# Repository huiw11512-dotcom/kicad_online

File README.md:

# Linux MiniHost A1

RK3568 ARM64 Linux SBC。目标是树莓派 4B 级别的独立 Linux 单板计算机，优先保证稳定启动、存储、显示、网络和 USB 接口；不宣称与树莓派 4B 的 CPU 性能相同。

## Rev1 首板基线

| 模块 | 首板方案 |
|---|---|
| SoC | Rockchip RK3568，FCBGA636 |
| RAM | 2GB LPDDR4X x32，Micron MT53E512M32D1ZW-046B WT:B，单颗、单 Die、单 Rank |
| 系统存储 | 32GB eMMC 5.1，Samsung KLMBG2JETD-B041 候选 |
| 扩展存储 | MicroSD，SDMMC0 4-bit |
| PMIC | RK809-5 |
| CPU 电源 | TCS4525_WT 独立动态 Buck，待完整时序与负载验证 |
| 输入 | USB-C PD 15V/3A |
| 主电源 | LM76005，15V_IN → 5V_SYS，5A 额定设计目标 |
| 预 PMIC 电源 | TPS62132，5V_SYS → 3.3V |
| PCB | 六层 FR-4；1.6mm 为初始目标，最终叠层与阻抗由板厂确认 |

4GB LPDDR4X 保留为后续容量版本，不混入本次 2GB 首板 BOM。4GB 候选虽也出现在公开 Rockchip DDR AVL v3.01 的 RK3568 T/A 项中，但其 D2/FW 双 Die 组织需要单独确认 rank、模板、BIN 与封装映射。

## 当前工程状态（2026-11-16）

**DESIGN IN PROGRESS — DO NOT FABRICATE**

KiCad 主工程已建立层级原理图：**1 张根页 + 12 张子页**。当前源文件结构如下：

1. 根页：USB-C PD、输入保护、15V→5V Buck
2. RK809-5 PMIC
3. DDR 电源
4. 预 PMIC 3.3V 电源
5. RK3568 SoC（17 个 unit）
6. CPU 动态 Buck
7. 32GB eMMC
8. Boot、时钟、复位、UART2 与 Recovery
9. Micron 2GB LPDDR4X
10. MicroSD
11. USB3 HOST1 与 USB-C OTG0 下载/恢复
12. USB2 HOST2/HOST3 两个独立 Type-A Host
13. 初步 Gigabit Ethernet PHY / MagJack 页面

### 已完成的源文件核对

- RK3568：636 个唯一球位；Pin assignment CSV 为 610 个已分配网络 + 26 个显式 NC。
- SoC 原理图 global labels 与 CSV 做坐标级交叉核对：0 个网络标签错配；26 个 NC 标记与 CSV 一致。
- USB2 HOST2/3：SoC R1/R2 对应 HOST2 D−/D+，T1/T2 对应 HOST3 D−/D+；此前误放在 K17/K18/M12/M17 电源球位上的 USB 标签已纠正。
- Wi-Fi/BT pinmux：由于 GMAC0 RGMII 与 SDMMC1 复用球位冲突，Wi-Fi 临时改分配到 SDMMC2 M0，Bluetooth UART 临时分配 UART8 M0。AP6275S 仍是候选；AMPAK Rev.2.7 与 LCSC C2918717 旧版在 pin33/pin35/pin48 存在差异，模块 padout/RF 端口、内部 Buck 网络和模块页未冻结。
- MicroSD：VCC 由 RK809-5 SWOUT2 控制；R57 0Ω 旁路为 DNP，不得装配。
- Ethernet：RTL8211F-CG + HR911130A 初步页已建立；PHY strap、电源、时钟、RGMII 延时、MagJack 引脚和网表审查仍未关闭。

以上是源文件结构与静态映射检查，不等于 KiCad 原生 ERC、网表、电气规则、PCB DRC 或硬件验证通过。

## 尚未完成

- HDMI 完整电路。
- Wi-Fi/BT 模块电路、AP6275S 50-pad footprint、3.3V VBAT/1.8V VDDIO、37.4MHz 晶体、1.8V/32.768kHz LPO 和唤醒控制。
- Ethernet PHY 逐引脚审查与千兆链路验证。
- 40-pin GPIO 最终 pinmux、电压域和连接器。
- 生产测试点、完整电源预算、热设计和局部去耦审查。
- 整板 PCB 布局尚未开始。

## 打开工程

GitHub 网页预览不会把整个 KiCad 层级工程渲染成一张可编辑原理图。请下载完整的 `hardware/kicad` 目录，保留其中的子原理图、符号库和封装库，再用桌面 KiCad 打开工程文件：

- [KiCad 工程文件 A1.kicad_pro](hardware/kicad/A1.kicad_pro)
- [根原理图 A1.kicad_sch](hardware/kicad/A1.kicad_sch)
- [完整 KiCad 工程目录](hardware/kicad/)
- [KiCad 工程说明](hardware/kicad/README.md)

## 关键设计文件

- [Rev1 主设计基线](docs/A1_MASTER_BASELINE_REV1.md)
- [电气实现决策](docs/A1_ELECTRICAL_DECISIONS_REV1.md)
- [Wi-Fi/BT pinmux 与电气基线](hardware/kicad/docs/A1_WIFI_BT_PINMUX_REV1.md)
- [Ethernet PHY 审查清单](hardware/kicad/docs/A1_ETHERNET_VALIDATION_REV1.md)
- [DDR 选型与兼容性门槛](docs/DDR_COMPATIBILITY_GATE.md)
- [DDR 首轮审计记录](docs/A1_DDR_AUDIT_2026-11-16.md)
- [Rockchip DDR 模板 / BIN 确认请求](docs/RK3568_DDR_FAE_REQUEST.md)

## 投板前硬门槛

1. 取得当前官方 Rockchip DDR AVL、精确模板文件、DDR BIN 和 WDQS 适用说明。
2. 完成 RK809-5 全部电源轨与上电时序逐网核对。
3. 完成 HDMI、Ethernet、Wi-Fi/BT、GPIO 等外围原理图。
4. 用原生 KiCad 执行 ERC、网表导出、封装检查和 PCB DRC。
5. 完成六层叠层、阻抗、DDR 拓扑/长度约束、BGA 扇出和电源完整性审查。
6. 首板完成 DDR Training、eMMC 启动、外设功能和联合压力测试。

在上述门槛关闭前，不发布制造版 Gerber、坐标文件或投板 BOM。

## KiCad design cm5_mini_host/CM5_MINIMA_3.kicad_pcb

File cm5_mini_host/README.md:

# CM5 MiniHost — high-speed carrier development

**Stage:** Rev.A engineering prototype derived from the attributed CM5 MINIMA reference. Native KiCad 10 schematic and PCB have been edited and cloud checked, but the board **has not been fabricated, signal-integrity validated, or released for manufacture**.

## Goal

A genuinely Linux-capable small computer using the **Raspberry Pi Compute Module 5**. Features to retain in our eventual custom revision:

- USB-C external 5 V supply and safe power sequencing
- HDMI display output
- Gigabit Ethernet
- PCIe Gen 2 ×1 to M.2 Key-M NVMe SSD
- USB 2.0 host/user interface (plus Wi-Fi/Bluetooth when the fitted CM5 supports it)
- Boot/service access, status indicators and thermal provisions

Unlike a microcontroller demo, CM5 includes CPU, RAM, and optional eMMC and can run Raspberry Pi OS.

## Origin and licensing

The starting electronic design is **CM5 MINIMA REV3** by Pierluigi Colangeli, source: https://github.com/piecol/CM5_MINIMA_REV3

Source snapshot commit: `6d77314dbbc26c8f5735add30ccb0588816cb71a`.

The original is open hardware under **CERN-OHL-S-2.0**. We retain the upstream license and identify changes in version history. Do not describe the baseline as independently designed or verified in this repository. See `SOURCE_README.md` after import.

## Manufacturing-risk BOM correction

**U602 corrected to Diodes 74LVC1G07SE-7 (JLC/LCSC C67531)** from the physically and logically incorrect SN74LVC1G14DBVR value. The existing schematic describes a non-inverting open-drain 1G07 that sinks the R605/D605 LED branch; original 1G14 was a SOT-23 Schmitt inverter, not pin/function/footprint-equivalent in practice. Both schematic P/N+Value and PCB P/N+Value fields synchronized and validated in KiCad: **ERC 0, hard DRC 2, parity 0, unconnected 0, total DRC 85 unchanged**. [U602 verified fix](U602_BOM_CORRECTION_AUDIT.md) / [root cause and remaining footprint checks](U602_COMPONENT_MISMATCH_REVIEW.md).

**Other footprint findings:** [50 mismatch summary](FOOTPRINT_MISMATCH_PAD_AUDIT.md) and [8 actual pad-by-pad comparison](EIGHT_FOOTPRINT_PAD_DELTA.md). Of the eight flagged devices, U602 had confirmed P/N/logic/package error; U1 LIS3DH and CM5 Module301 have a bottom-side coordinate-mirroring effect that must be normalized before interpreting pad offsets as routing faults; J701 difference involves alternate mounting holes. Do not automatically replace stock footprints to silence warnings.

## Latest verified board status — 2026-11-14

**Latest MiniHost-specific native KiCad 10.0.8 run:** [CI run 43606720543](https://github.com/huiw11512-dotcom/kicad_online/actions/runs/43606720543). Results: **ERC 0 errors / 41 warnings; PCB DRC 0 hard errors / 73 warnings; 0 unconnected pads; 0 schematic-to-PCB footprint parity errors.** The 73 PCB warnings are 49 embedded-vs-library footprint differences, 15 silk-edge, 8 silk-overlap and 1 silk-over-copper. They are still subject to review; no warning classes have been globally disabled.

The two RJ45 shield pad-to-edge hard errors have now been resolved by a controlled +0.030 mm notch/fillet adjustment and a manufacturer/fabricator-specific 0.20 mm J1 edge-clearance allowance, while retaining the enhanced 0.372 mm target elsewhere. U602 has also been corrected to Diodes 74LVC1G07SE-7 with its vendor SOT-353 land pattern. **The board is still not fabrication released**: ERC warnings, PCB warnings, stackup-controlled SI/PI, thermal/power and enclosure fit remain.

[Latest detailed verification and release gates](REV_A_LATEST_VERIFICATION.md) · [Latest warning-by-warning triage](DRC_WARNING_TRIAGE.md) · [Power and USB review](POWER_AND_USB_REVIEW.md).

## Rev.A completed and verified (2026-11-14)

- Reproduced actual six-layer CM5 Linux carrier in the native KiCad and web viewer.
- Repaired USB-C root bus naming and verified **4/4 D+/D− schematic-net-to-PCB-pad networks match**.
- Routed one tested USB701 A7 N backside branch from 6.4241 to 4.2503 mm copper centerline; before/after **4 → 4 hard DRC** and **0 → 0 unconnected**. This is not SI signoff.
- Recovered **8 custom PCB-embedded footprint types** into locally registered EasyEDA, Samacsys and _pico libraries, passing KiCad export/reimport pad checks.
- Reconciled the M.2 socket schematic's four nonexistent alternative mechanical pins M1..M4 against the installed 2230/2242 connector footprint.
- Adjusted **R701 15k→39k and R702/R703 22k→56k** in the native schematic and PCB for 500mA default-current USB2 host, with no DRC regression.
- Replaced the oversize rectangular RJ45 F.CrtYd with a **closed pad-aware 12-edge courtyard** in both board and project library: hard errors **4→2** and courtyard overlaps **2→0**, no electrical geometry changes.
- Reconciled conflicting duplicate CM5 NPTH drills: Module301 had **2.7 mm** holes, Module302 had **3.0 mm** holes in the very same locations. Preserved 2.7 mm M2.5 mounting holes and removed duplicate 3.0 mm holes, syncing the HSS project footprint. Native cloud report: **holes_co_located 2→0**, and **ERC/hard DRC/parity/unconnected stayed 0/2/0/0**.
- Initialized official KiCad 10 standard global footprint and symbol tables in CI to remove 65 false missing-library warnings; classified remaining DRC warnings without disabling them.
- Removed duplicate large CM5 outline from Module302/HSS only, leaving GPIO body outline and HSS connector marks: **230→198 DRC entries**.
- Properly hid 27 near-zero KiBuzzard autogenerated reference fields (without removing any visible polygon labels): **198→140 DRC entries**.
- Replaced J701 M.2's per-pad mask expansion 0.102→0.020 mm for its 69 SMT pads; copper/pitch untouched and 0.16 mm nominal mask web for a proposed 1oz green LDI process: **140→86**.
- Removed one redundant USB-C D+ via linking two same-layer F.Cu trace endpoints; net parity and DRC remained safe: **86→85**. Two other flagged vias require stub-level inspection and were retained.
- Removed one pad-free PCB-only demonstration logo footprint REF** (upstream license and attribution preserved).
- Latest *verified* electrical/DFM check after these changes: **ERC 0 errors, PCB schematic/footprint parity 0 issues, PCB unconnected 0**, with **2 remaining hard DRC errors** at the Kycon RJ45 shield solder pads and adjacent board-edge opening. Warnings still exist and require review.

## Current blockers / engineering documents

- [Verified RJ45 pad-aware courtyard audit](RJ45_COURTYARD_RESHAPE_AUDIT.md)
- [500mA USB host change audit](USB_POWER_500MA_AUDIT.md)
- [RJ45 physical conflict map](RJ45_MECHANICAL_CONFLICT_MAP.svg) and [manufacturer-grounded mechanical review](RJ45_MECHANICAL_REVIEW.md): J1 pads 15/16 board-edge hard errors resolved; physical connector/enclosure overhang still requires validation; the previous J1/J601 and J1/H102 courtyard overlaps were removed via geometry verified by KiCad
- [M.2 symbol/footprint verification](M2_SYMBOL_VARIANT_AUDIT.md) and [decorative logo cleanup verification](LOGO_CLEANUP_AUDIT.md)
- [Power, USB, CM5 5V/5A budget and startup review](POWER_AND_USB_REVIEW.md)
- [Controlled USB701 reroute and DRC no-regression](USB_REROUTE_AUDIT.md)
- [Actual KiCad 10 DRC warning triage](DRC_WARNING_TRIAGE.md) and [CM5 duplicate NPTH hole repair](CM5_ALIGNMENT_HOLE_AUDIT.md)
- [Original baseline audit — historical, before Rev.A corrections](AUDIT_2026-11-14.md)

**Next implementation gate:** resolve the two RJ45 shield solder land copper-to-edge gap violations based on Kycon's required PCB opening and full enclosure clearance; updated pad-aware courtyard eliminated two false overlaps and was verified with KiCad. Follow with exact factory stackup-controlled differential impedance, component datasheet verification, full PI/thermal checks, and a prototype bring-up plan. No release Gerbers have been approved.

## Open in ZiroEDA

https://designer.ziroeda.com/gh/huiw11512-dotcom/kicad_online/tree/minihost-revA/cm5_mini_host

If the deep link fails, use ZiroEDA → File → Open from GitHub, select `huiw11512-dotcom/kicad_online` → `cm5_mini_host` → `CM5_MINIMA_3.kicad_pro`.

This baseline includes complete routed source files; 3D manufacturer models may be omitted where large. Missing external 3D models do not affect native copper geometry.

## Important

Do **not** order boards based solely on a successful web import. Proper fabrication release requires electrical design review, pin-map and component-footprint verification, stackup and impedance calculation from the board fabricator, complete DRC/ERC closure, Gerber/NC drill and stencil review, and bench bring-up.

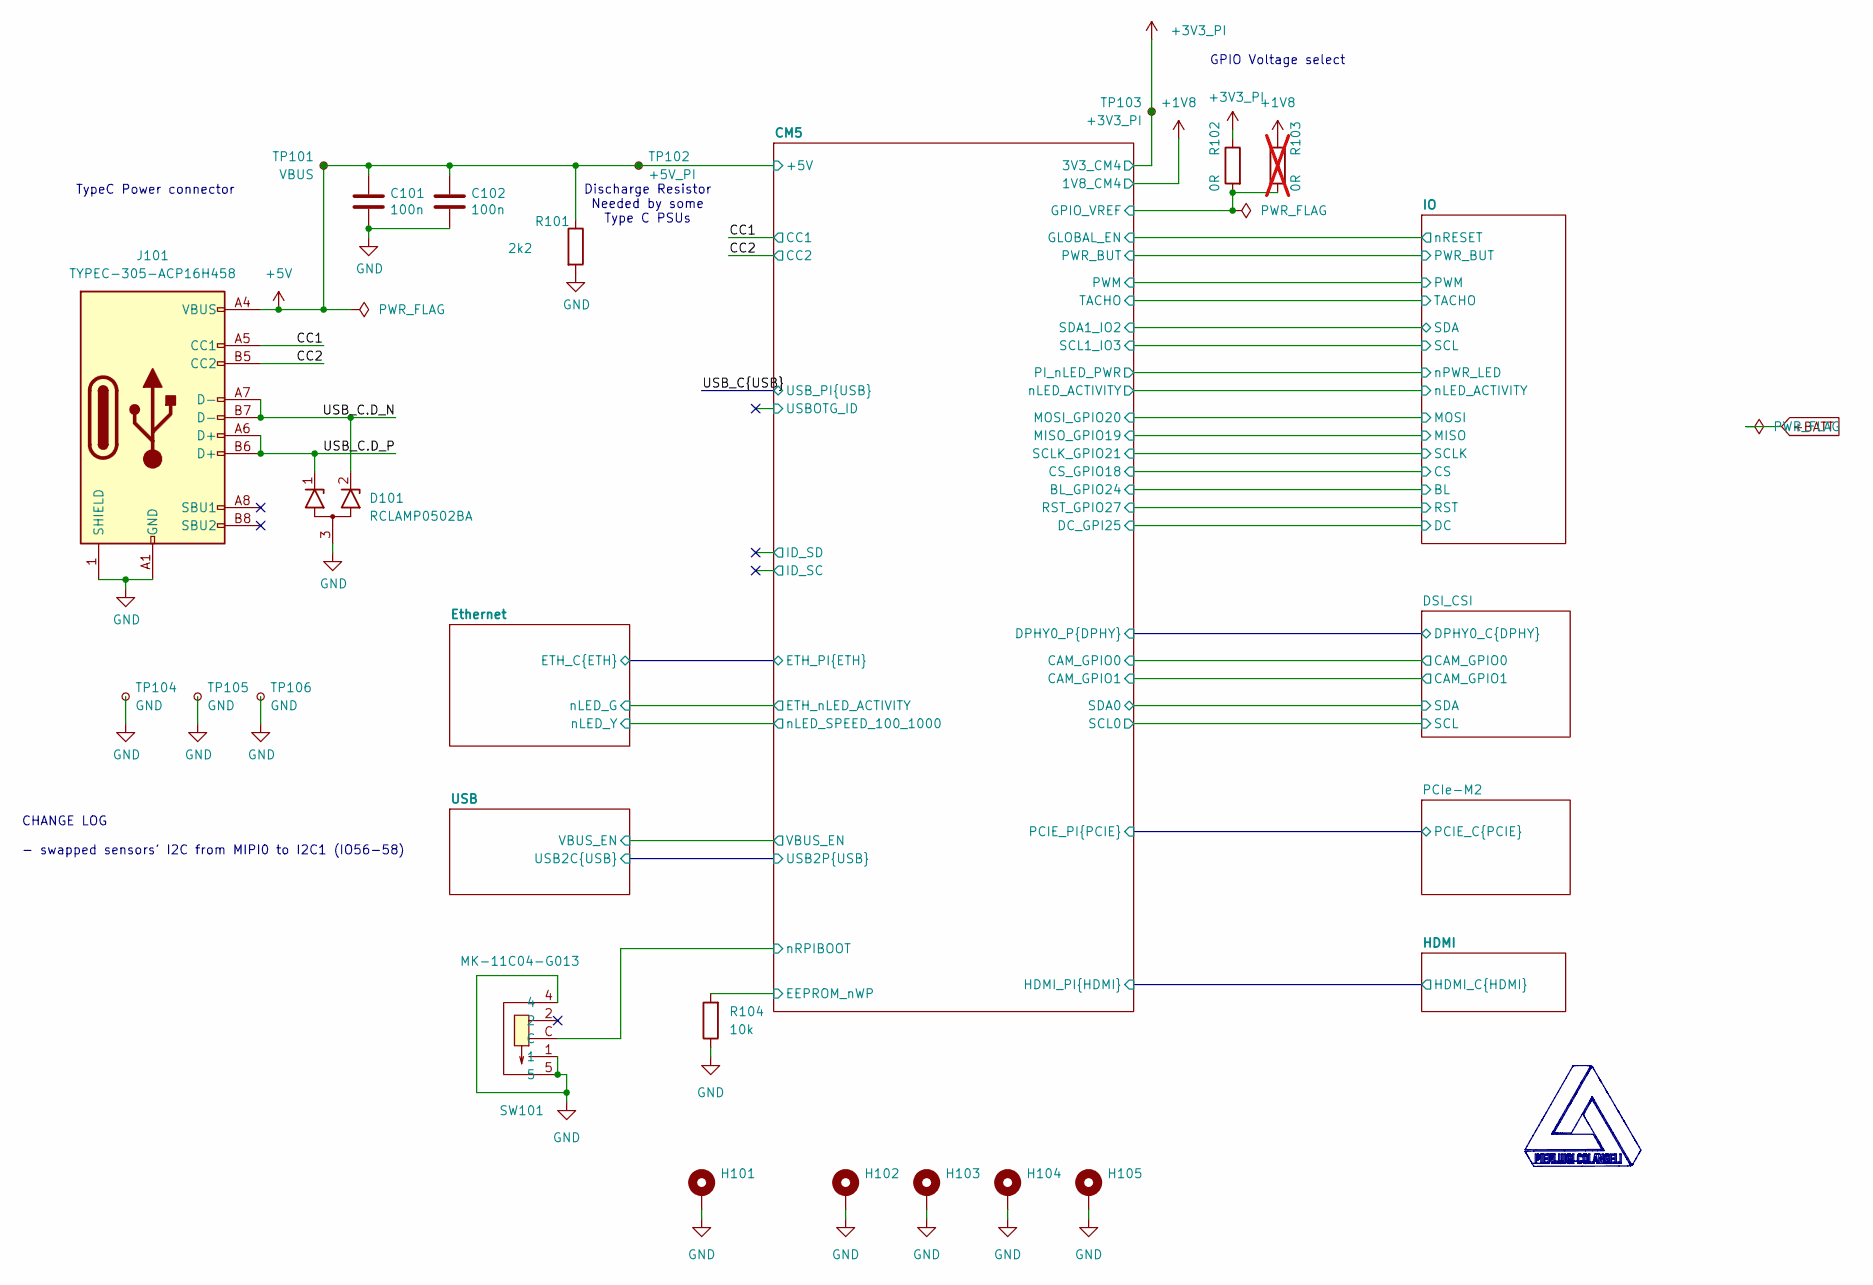
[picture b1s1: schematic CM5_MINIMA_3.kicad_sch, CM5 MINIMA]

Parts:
C101, C102: 100n; C_0402_1005Metric; Part Description 0.1uF 10% 16V Ceramic Capacitor X7R 040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
D101: RCLAMP0502BA; SOT-416
H101: MountingHole_Pad; MountingHole_2.2mm_M2_DIN965_Pad_TopBottom
H102, H103, H104, H105: MountingHole_Pad; MountingHole_2.7mm_Pad
J101: TYPEC-305-ACP16H458; USB-C-SMD_TYPEC-305-ACP16H458; Part Description USBC USB2 data and power connector
R101: 2k2; R_0402_1005Metric
R102: 0R; R_0402_1005Metric; Part Description Resistor 0R M2012 5%
R103: 0R; R_0402_1005Metric; not fitted
R104: 10k; R_0402_1005Metric
SW101: MK-11C04-G013; SW-SMD_MK-11C04-G013; LCSC Part C778185
TP101: VBUS; TestPoint_Pad_D1.0mm__TP101
TP102: +5V_PI; TestPoint_Pad_D1.0mm
TP103: +3V3_PI; TestPoint_Pad_D1.0mm
TP104, TP105, TP106: GND; TestPoint_THTPad_D1.0mm_Drill0.5mm

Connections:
+1V8: R103.1; also elsewhere on the board
+3V3_PI: R102.1, TP103.1; also elsewhere on the board
+5V: C101.1, C102.1, J101.A4 (VBUS), J101.A9 (VBUS), J101.B4 (VBUS), J101.B9 (VBUS), R101.1, TP101.1, TP102.1; also elsewhere on the board
/CC1: J101.A5 (CC1); also elsewhere on the board
/CC2: J101.B5 (CC2); also elsewhere on the board
/CM5/EEPROM_nWP: R104.2; also elsewhere on the board
/CM5/GPIO_VREF: R102.2, R103.2; also elsewhere on the board
/CM5/nRPIBOOT: SW101.C; also elsewhere on the board
/USB_C.D_N: D101.2 (K2), J101.A7 (D-), J101.B7 (D-); also elsewhere on the board
/USB_C.D_P: D101.1 (K1), J101.A6 (D+), J101.B6 (D+); also elsewhere on the board
GND: C101.2, C102.2, D101.3 (A), H101.1, H102.1, H103.1, H104.1, H105.1, J101.1 (SHIELD), J101.A1 (GND), J101.A12 (GND), J101.B1 (GND), J101.B12 (GND), R101.2, R104.1, SW101.1, SW101.4, SW101.5, TP104.1, TP105.1, TP106.1; also elsewhere on the board

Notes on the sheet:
CHANGE LOG - swapped sensors' I2C from MIPI0 to I2C1 (IO56-58)
GPIO Voltage select
TypeC Power connector
Discharge Resistor Needed by some Type C PSUs

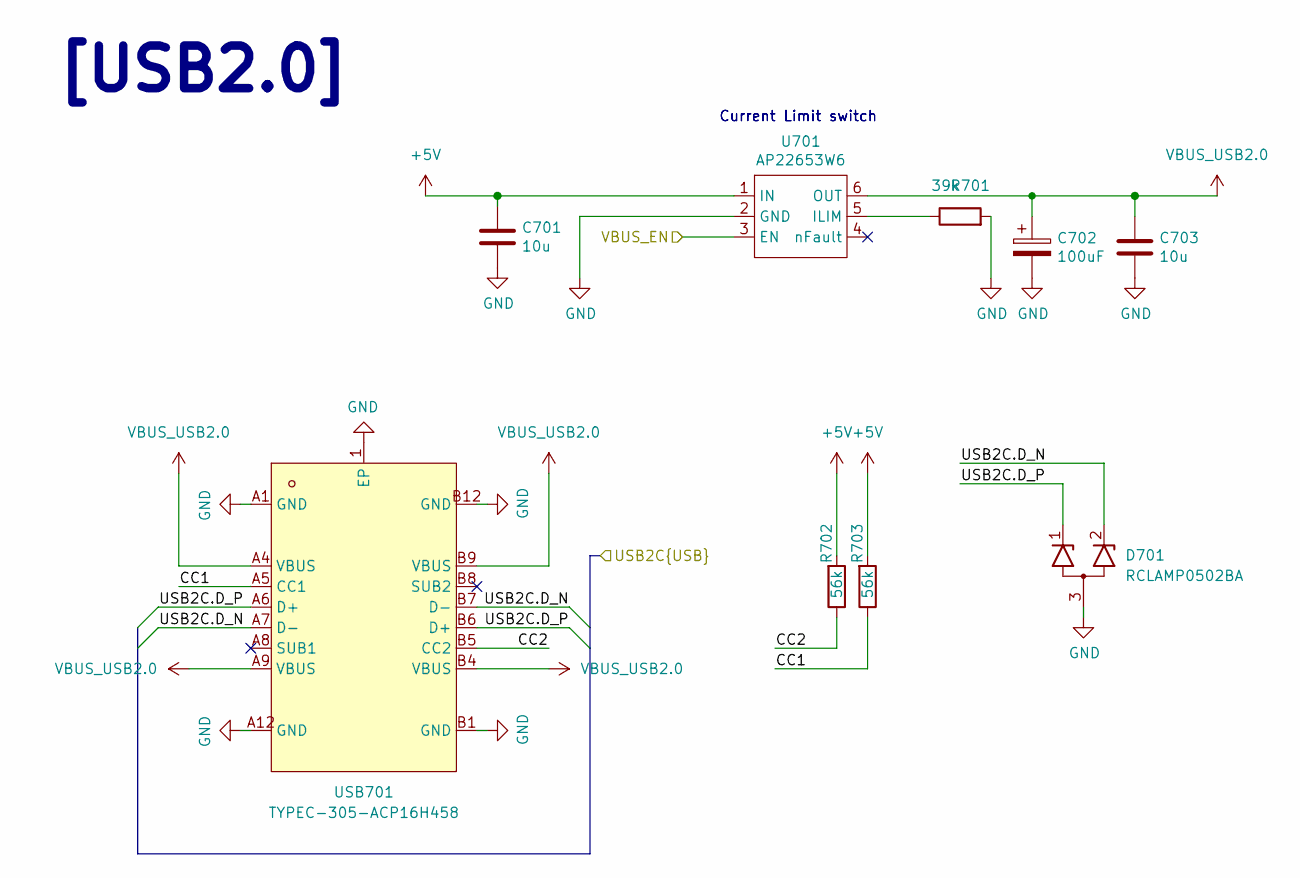
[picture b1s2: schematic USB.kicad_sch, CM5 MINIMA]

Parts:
C701, C703: 10u; C_0805_2012Metric; Part Description 10uF 10% 10V Ceramic Capacitor X7R 0805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
C702: 100uF; CP_EIA-3528-21_Kemet-B; Part Description 100uF 6.3V 1.7Ω@100kHz ±10% CASE-B-3528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
D701: RCLAMP0502BA; SOT-416__D701
R701: 39k; R_0402_1005Metric; Part Description Resistor 15K M1005 1% 63mW
R702, R703: 56k; R_0402_1005Metric__R702__R703
U701: AP22653W6; SOT-23-6; Part Description Power Switch/Driver 1:1 P-Channel 2.1A 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
USB701: TYPEC-305-ACP16H458; USB-C-SMD_TYPEC-305-ACP16H458; LCSC Part C5454943

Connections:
+5V: C701.1, R702.2, R703.2, U701.1 (IN); also elsewhere on the board
/CM5/USB2P.D_N: D701.2 (K2), USB701.A7 (D-), USB701.B7 (D-); also elsewhere on the board
/CM5/USB2P.D_P: D701.1 (K1), USB701.A6 (D+), USB701.B6 (D+); also elsewhere on the board
/CM5/VBUS_EN: U701.3 (EN); also elsewhere on the board
/USB/CC1: R703.1, USB701.A5 (CC1)
/USB/CC2: R702.1, USB701.B5 (CC2)
GND: C701.2, C702.2, C703.2, D701.3 (A), R701.2, U701.2 (GND), USB701.1 (EP), USB701.A1 (GND), USB701.A12 (GND), USB701.B1 (GND), USB701.B12 (GND); also elsewhere on the board
unnamed: R701.1, U701.5 (ILIM)
VBUS_USB2.0: C702.1, C703.1, U701.6 (OUT), USB701.A4 (VBUS), USB701.A9 (VBUS), USB701.B4 (VBUS), USB701.B9 (VBUS)

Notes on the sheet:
[USB2.0]
Current Limit switch

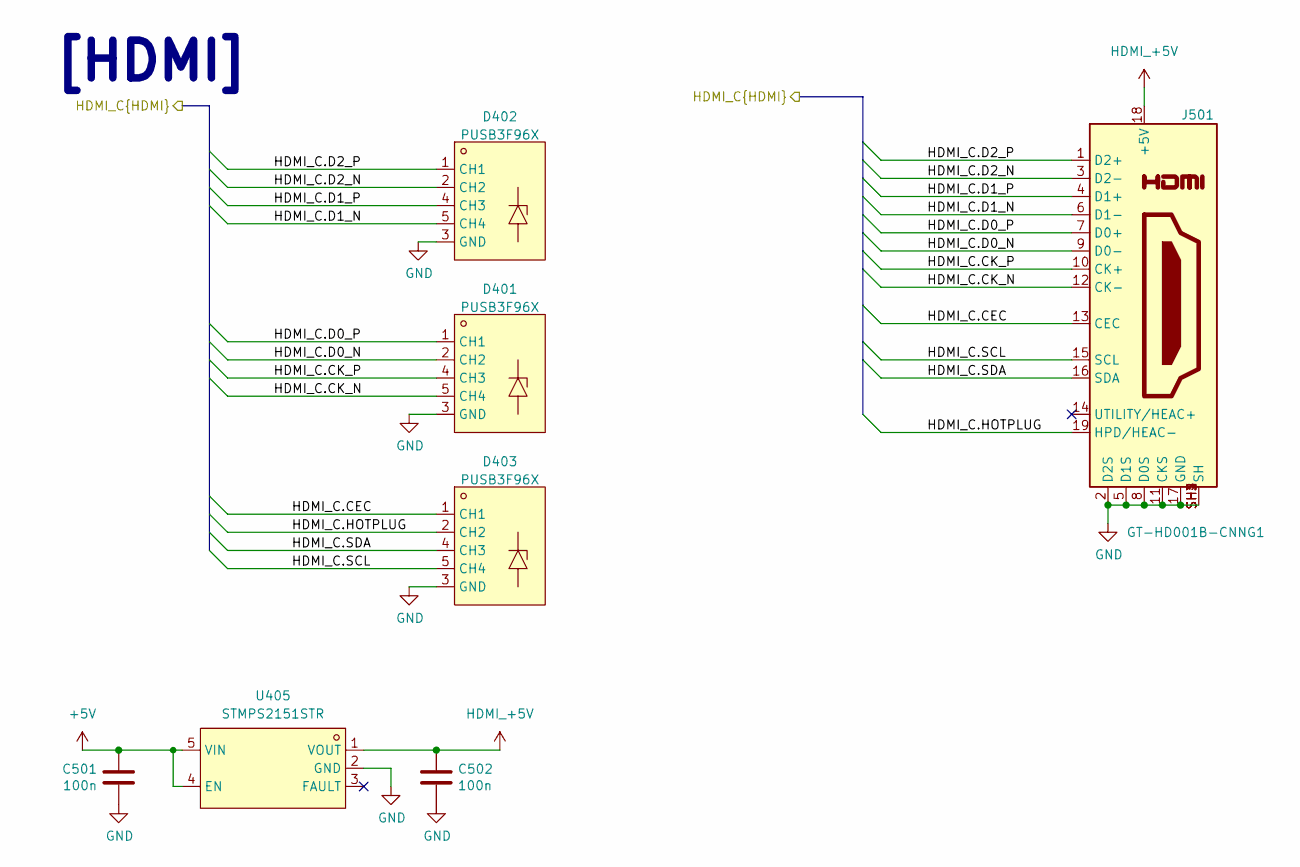
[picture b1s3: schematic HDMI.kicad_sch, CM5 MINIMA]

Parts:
C501, C502: 100n; C_0402_1005Metric; Part Description 0.1uF 10% 16V Ceramic Capacitor X7R 040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
D401, D402, D403: PUSB3F96X; DFN2510A-10_L2.5-W1.0-P0.50-BL; LCSC Part C478121
J501: GT-HD001B-CNNG1; EDAC 690-019-298-412; Part Description HDMI Connector, Right Angle, 19 Contact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
U405: STMPS2151STR; SOT-23-5; LCSC Part C135998

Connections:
+5V: C501.1, U405.4 (EN), U405.5 (VIN); also elsewhere on the board
/CM5/HDMI_PI.CEC: D403.1 (CH1), D403.10 (NC), J501.13 (CEC); also elsewhere on the board
/CM5/HDMI_PI.CK_N: D401.5 (CH4), D401.6 (NC), J501.12 (CK-); also elsewhere on the board
/CM5/HDMI_PI.CK_P: D401.4 (CH3), D401.7 (NC), J501.10 (CK+); also elsewhere on the board
/CM5/HDMI_PI.D0_N: D401.2 (CH2), D401.9 (NC), J501.9 (D0-); also elsewhere on the board
/CM5/HDMI_PI.D0_P: D401.1 (CH1), D401.10 (NC), J501.7 (D0+); also elsewhere on the board
/CM5/HDMI_PI.D1_N: D402.5 (CH4), D402.6 (NC), J501.6 (D1-); also elsewhere on the board
/CM5/HDMI_PI.D1_P: D402.4 (CH3), D402.7 (NC), J501.4 (D1+); also elsewhere on the board
/CM5/HDMI_PI.D2_N: D402.2 (CH2), D402.9 (NC), J501.3 (D2-); also elsewhere on the board
/CM5/HDMI_PI.D2_P: D402.1 (CH1), D402.10 (NC), J501.1 (D2+); also elsewhere on the board
/CM5/HDMI_PI.HOTPLUG: D403.2 (CH2), D403.9 (NC), J501.19 (HPD/HEAC-); also elsewhere on the board
/CM5/HDMI_PI.SCL: D403.5 (CH4), D403.6 (NC), J501.15 (SCL); also elsewhere on the board
/CM5/HDMI_PI.SDA: D403.4 (CH3), D403.7 (NC), J501.16 (SDA); also elsewhere on the board
GND: C501.2, C502.2, D401.3 (GND), D401.8 (GND), D402.3 (GND), D402.8 (GND), D403.3 (GND), D403.8 (GND), J501.2 (D2S), J501.5 (D1S), J501.8 (D0S), J501.11 (CKS), J501.17 (GND), J501.SH1 (SH), J501.SH2 (SH), J501.SH3 (SH), J501.SH4 (SH), U405.2 (GND); also elsewhere on the board
HDMI_+5V: C502.1, J501.18 (+5V), U405.1 (VOUT)

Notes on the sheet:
[HDMI]

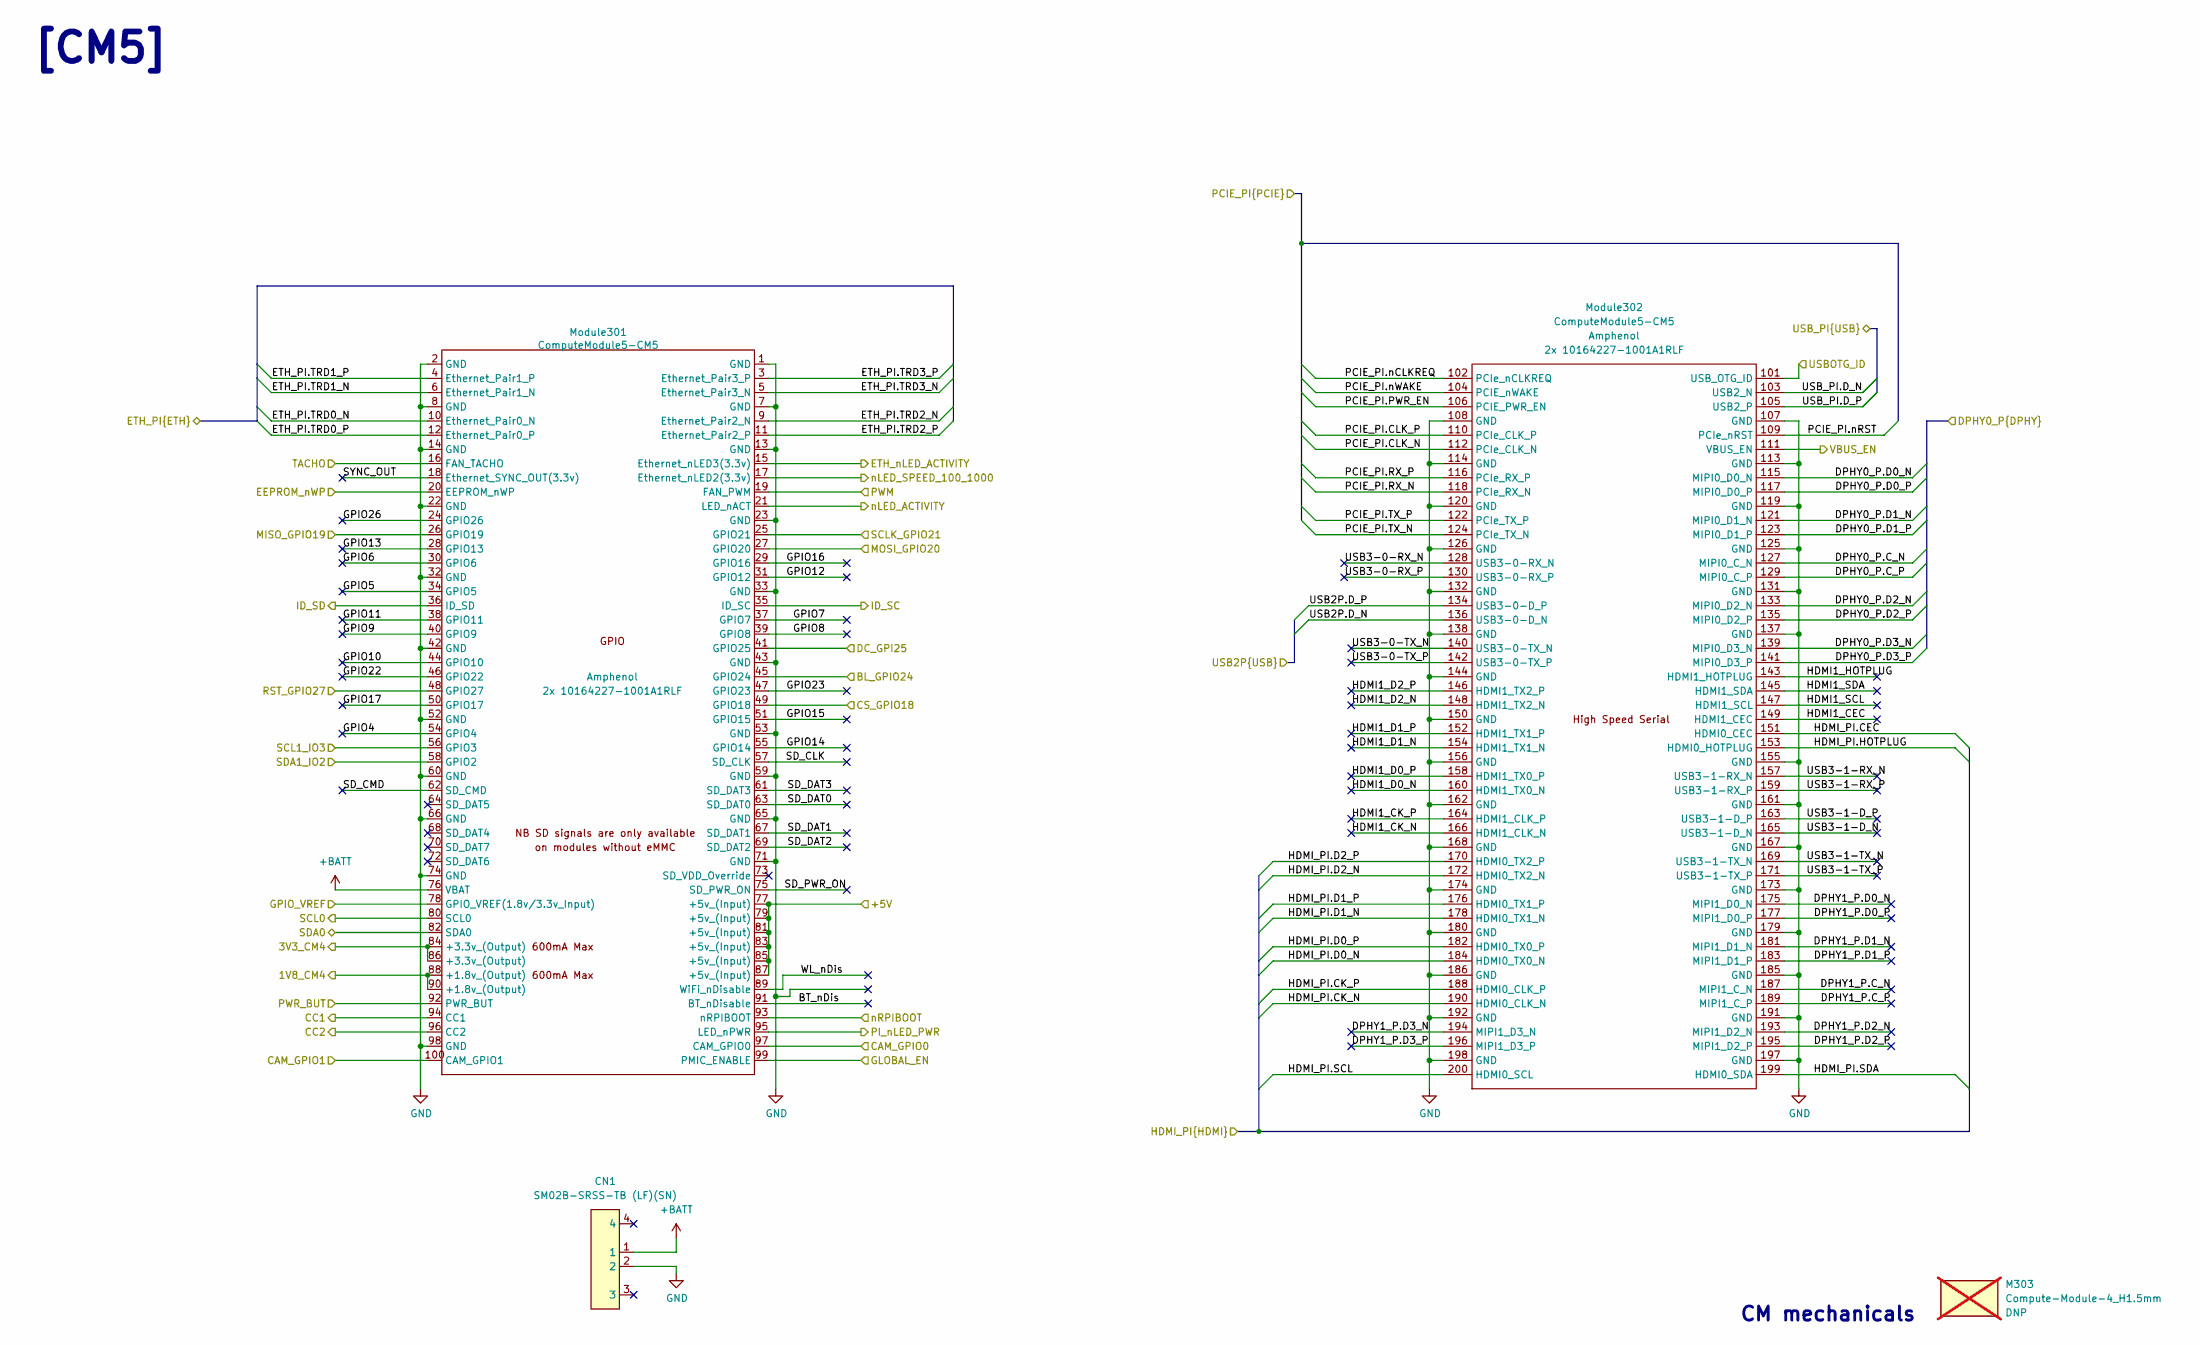
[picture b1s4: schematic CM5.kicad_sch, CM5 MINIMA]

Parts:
CN1: SM02B-SRSS-TB (LF)(SN); CONN-SMD_2P-P1.00_SM02B-SRSS-TB-LF-SN; LCSC Part C160402
M303: Compute-Module-4_H1.5mm; MPN SC0294; not fitted
Module301: ComputeModule5-CM5; Raspberry-Pi-5-Compute-Module_GPIO; Part Description 100 Position Connector Receptacle, Cent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
Module302: ComputeModule5-CM5; Raspberry-Pi-5-Compute-Module_HSS; Part Description 100 Position Connector Receptacle, Cent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

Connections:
+1V8: Module301.88 (+1.8v_(Output)), Module301.90 (+1.8v_(Output)); also elsewhere on the board
+3V3_PI: Module301.84 (+3.3v_(Output)), Module301.86 (+3.3v_(Output)); also elsewhere on the board
+5V: Module301.77 (+5v_(Input)), Module301.79 (+5v_(Input)), Module301.81 (+5v_(Input)), Module301.83 (+5v_(Input)), Module301.85 (+5v_(Input)), Module301.87 (+5v_(Input)); also elsewhere on the board
+BATT: CN1.1, Module301.76 (VBAT)
/CC1: Module301.94 (CC1); also elsewhere on the board
/CC2: Module301.96 (CC2); also elsewhere on the board
/CM5/BL_GPIO24: Module301.45 (GPIO24); also elsewhere on the board
/CM5/BT_nDis: Module301.91 (BT_nDisable)
/CM5/CAM_GPIO0: Module301.97 (CAM_GPIO0); also elsewhere on the board
/CM5/CAM_GPIO1: Module301.100 (CAM_GPIO1); also elsewhere on the board
/CM5/CS_GPIO18: Module301.49 (GPIO18); also elsewhere on the board
/CM5/DC_GPI25: Module301.41 (GPIO25); also elsewhere on the board
/CM5/DPHY0_P.C_N: Module302.127 (MIPI0_C_N); also elsewhere on the board
/CM5/DPHY0_P.C_P: Module302.129 (MIPI0_C_P); also elsewhere on the board
/CM5/DPHY0_P.D0_N: Module302.115 (MIPI0_D0_N); also elsewhere on the board
/CM5/DPHY0_P.D0_P: Module302.117 (MIPI0_D0_P); also elsewhere on the board
/CM5/DPHY0_P.D1_N: Module302.121 (MIPI0_D1_N); also elsewhere on the board
/CM5/DPHY0_P.D1_P: Module302.123 (MIPI0_D1_P); also elsewhere on the board
/CM5/DPHY0_P.D2_N: Module302.133 (MIPI0_D2_N); also elsewhere on the board
/CM5/DPHY0_P.D2_P: Module302.135 (MIPI0_D2_P); also elsewhere on the board
/CM5/DPHY0_P.D3_N: Module302.139 (MIPI0_D3_N); also elsewhere on the board
/CM5/DPHY0_P.D3_P: Module302.141 (MIPI0_D3_P); also elsewhere on the board
/CM5/DPHY1_P.C_N: Module302.187 (MIPI1_C_N)
/CM5/DPHY1_P.C_P: Module302.189 (MIPI1_C_P)
/CM5/DPHY1_P.D0_N: Module302.175 (MIPI1_D0_N)
/CM5/DPHY1_P.D0_P: Module302.177 (MIPI1_D0_P)
/CM5/DPHY1_P.D1_N: Module302.181 (MIPI1_D1_N)
/CM5/DPHY1_P.D1_P: Module302.183 (MIPI1_D1_P)
/CM5/DPHY1_P.D2_N: Module302.193 (MIPI1_D2_N)
/CM5/DPHY1_P.D2_P: Module302.195 (MIPI1_D2_P)
/CM5/DPHY1_P.D3_N: Module302.194 (MIPI1_D3_N)
/CM5/DPHY1_P.D3_P: Module302.196 (MIPI1_D3_P)
/CM5/EEPROM_nWP: Module301.20 (EEPROM_nWP); also elsewhere on the board
/CM5/ETH_PI.TRD0_N: Module301.10 (Ethernet_Pair0_N); also elsewhere on the board
/CM5/ETH_PI.TRD0_P: Module301.12 (Ethernet_Pair0_P); also elsewhere on the board
/CM5/ETH_PI.TRD1_N: Module301.6 (Ethernet_Pair1_N); also elsewhere on the board
/CM5/ETH_PI.TRD1_P: Module301.4 (Ethernet_Pair1_P); also elsewhere on the board
/CM5/ETH_PI.TRD2_N: Module301.9 (Ethernet_Pair2_N); also elsewhere on the board
/CM5/ETH_PI.TRD2_P: Module301.11 (Ethernet_Pair2_P); also elsewhere on the board
/CM5/ETH_PI.TRD3_N: Module301.5 (Ethernet_Pair3_N); also elsewhere on the board
/CM5/ETH_PI.TRD3_P: Module301.3 (Ethernet_Pair3_P); also elsewhere on the board
/CM5/ETH_nLED_ACTIVITY: Module301.15 (Ethernet_nLED3(3.3v)); also elsewhere on the board
/CM5/GLOBAL_EN: Module301.99 (PMIC_ENABLE)
/CM5/GPIO4: Module301.54 (GPIO4)
/CM5/GPIO5: Module301.34 (GPIO5)
/CM5/GPIO6: Module301.30 (GPIO6)
/CM5/GPIO7: Module301.37 (GPIO7)
/CM5/GPIO8: Module301.39 (GPIO8)
/CM5/GPIO9: Module301.40 (GPIO9)
/CM5/GPIO10: Module301.44 (GPIO10)
/CM5/GPIO11: Module301.38 (GPIO11)
/CM5/GPIO12: Module301.31 (GPIO12)
/CM5/GPIO13: Module301.28 (GPIO13)
/CM5/GPIO14: Module301.55 (GPIO14)
/CM5/GPIO15: Module301.51 (GPIO15)
/CM5/GPIO16: Module301.29 (GPIO16)
/CM5/GPIO17: Module301.50 (GPIO17)
/CM5/GPIO22: Module301.46 (GPIO22)
/CM5/GPIO23: Module301.47 (GPIO23)
/CM5/GPIO26: Module301.24 (GPIO26)
/CM5/GPIO_VREF: Module301.78 (GPIO_VREF(1.8v/3.3v_Input)); also elsewhere on the board
/CM5/HDMI1_CEC: Module302.149 (HDMI1_CEC)
/CM5/HDMI1_CK_N: Module302.166 (HDMI1_CLK_N)
/CM5/HDMI1_CK_P: Module302.164 (HDMI1_CLK_P)
/CM5/HDMI1_D0_N: Module302.160 (HDMI1_TX0_N)
/CM5/HDMI1_D0_P: Module302.158 (HDMI1_TX0_P)
/CM5/HDMI1_D1_N: Module302.154 (HDMI1_TX1_N)
/CM5/HDMI1_D1_P: Module302.152 (HDMI1_TX1_P)
/CM5/HDMI1_D2_N: Module302.148 (HDMI1_TX2_N)
/CM5/HDMI1_D2_P: Module302.146 (HDMI1_TX2_P)
/CM5/HDMI1_HOTPLUG: Module302.143 (HDMI1_HOTPLUG)
/CM5/HDMI1_SCL: Module302.147 (HDMI1_SCL)
/CM5/HDMI1_SDA: Module302.145 (HDMI1_SDA)
/CM5/HDMI_PI.CEC: Module302.151 (HDMI0_CEC); also elsewhere on the board
/CM5/HDMI_PI.CK_N: Module302.190 (HDMI0_CLK_N); also elsewhere on the board
/CM5/HDMI_PI.CK_P: Module302.188 (HDMI0_CLK_P); also elsewhere on the board
/CM5/HDMI_PI.D0_N: Module302.184 (HDMI0_TX0_N); also elsewhere on the board
/CM5/HDMI_PI.D0_P: Module302.182 (HDMI0_TX0_P); also elsewhere on the board
/CM5/HDMI_PI.D1_N: Module302.178 (HDMI0_TX1_N); also elsewhere on the board
/CM5/HDMI_PI.D1_P: Module302.176 (HDMI0_TX1_P); also elsewhere on the board
/CM5/HDMI_PI.D2_N: Module302.172 (HDMI0_TX2_N); also elsewhere on the board
/CM5/HDMI_PI.D2_P: Module302.170 (HDMI0_TX2_P); also elsewhere on the board
/CM5/HDMI_PI.HOTPLUG: Module302.153 (HDMI0_HOTPLUG); also elsewhere on the board
/CM5/HDMI_PI.SCL: Module302.200 (HDMI0_SCL); also elsewhere on the board
/CM5/HDMI_PI.SDA: Module302.199 (HDMI0_SDA); also elsewhere on the board
/CM5/ID_SC: Module301.35 (ID_SC)
/CM5/ID_SD: Module301.36 (ID_SD)
/CM5/MISO_GPIO19: Module301.26 (GPIO19); also elsewhere on the board
/CM5/MOSI_GPIO20: Module301.27 (GPIO20); also elsewhere on the board
/CM5/PCIE_PI.CLK_N: Module302.112 (PCIe_CLK_N); also elsewhere on the board
/CM5/PCIE_PI.CLK_P: Module302.110 (PCIe_CLK_P); also elsewhere on the board
/CM5/PCIE_PI.PWR_EN: Module302.106 (PCIE_PWR_EN); also elsewhere on the board
/CM5/PCIE_PI.RX_N: Module302.118 (PCIe_RX_N); also elsewhere on the board
/CM5/PCIE_PI.RX_P: Module302.116 (PCIe_RX_P); also elsewhere on the board
/CM5/PCIE_PI.TX_N: Module302.124 (PCIe_TX_N); also elsewhere on the board
/CM5/PCIE_PI.TX_P: Module302.122 (PCIe_TX_P); also elsewhere on the board
/CM5/PCIE_PI.nCLKREQ: Module302.102 (PCIe_nCLKREQ); also elsewhere on the board
/CM5/PCIE_PI.nRST: Module302.109 (PCIe_nRST); also elsewhere on the board
/CM5/PCIE_PI.nWAKE: Module302.104 (PCIE_nWAKE); also elsewhere on the board
/CM5/PI_nLED_PWR: Module301.95 (LED_nPWR); also elsewhere on the board
/CM5/PWM: Module301.19 (FAN_PWM); also elsewhere on the board
/CM5/PWR_BUT: Module301.92 (PWR_BUT); also elsewhere on the board
/CM5/RST_GPIO27: Module301.48 (GPIO27); also elsewhere on the board
/CM5/SCL0: Module301.80 (SCL0); also elsewhere on the board
/CM5/SCLK_GPIO21: Module301.25 (GPIO21); also elsewhere on the board
/CM5/SDA0: Module301.82 (SDA0); also elsewhere on the board
/CM5/SD_CLK: Module301.57 (SD_CLK)
/CM5/SD_CMD: Module301.62 (SD_CMD)
/CM5/SD_DAT0: Module301.63 (SD_DAT0)
/CM5/SD_DAT1: Module301.67 (SD_DAT1)
/CM5/SD_DAT2: Module301.69 (SD_DAT2)
/CM5/SD_DAT3: Module301.61 (SD_DAT3)
/CM5/SD_PWR_ON: Module301.75 (SD_PWR_ON)
/CM5/SYNC_OUT: Module301.18 (Ethernet_SYNC_OUT(3.3v))
/CM5/TACHO: Module301.16 (FAN_TACHO); also elsewhere on the board
/CM5/USB2P.D_N: Module302.136 (USB3-0-D_N); also elsewhere on the board
/CM5/USB2P.D_P: Module302.134 (USB3-0-D_P); also elsewhere on the board
/CM5/USB3-0-RX_N: Module302.128 (USB3-0-RX_N)
/CM5/USB3-0-RX_P: Module302.130 (USB3-0-RX_P)
/CM5/USB3-0-TX_N: Module302.140 (USB3-0-TX_N)
/CM5/USB3-0-TX_P: Module302.142 (USB3-0-TX_P)
/CM5/USB3-1-D_N: Module302.165 (USB3-1-D_N)
/CM5/USB3-1-D_P: Module302.163 (USB3-1-D_P)
/CM5/USB3-1-RX_N: Module302.157 (USB3-1-RX_N)
/CM5/USB3-1-RX_P: Module302.159 (USB3-1-RX_P)
/CM5/USB3-1-TX_N: Module302.169 (USB3-1-TX_N)
/CM5/USB3-1-TX_P: Module302.171 (USB3-1-TX_P)
/CM5/USBOTG_ID: Module302.101 (USB_OTG_ID)
/CM5/VBUS_EN: Module302.111 (VBUS_EN); also elsewhere on the board
/CM5/WL_nDis: Module301.89 (WiFi_nDisable)
/CM5/nLED_ACTIVITY: Module301.21 (LED_nACT); also elsewhere on the board
/CM5/nLED_SPEED_100_1000: Module301.17 (Ethernet_nLED2(3.3v)); also elsewhere on the board
/CM5/nRPIBOOT: Module301.93 (nRPIBOOT); also elsewhere on the board
/IO/SCL: Module301.56 (GPIO3); also elsewhere on the board
/IO/SDA: Module301.58 (GPIO2); also elsewhere on the board
/USB_C.D_N: Module302.103 (USB2_N); also elsewhere on the board
/USB_C.D_P: Module302.105 (USB2_P); also elsewhere on the board
GND: CN1.2, Module301.1 (GND), Module301.2 (GND), Module301.7 (GND), Module301.8 (GND), Module301.13 (GND), Module301.14 (GND), Module301.22 (GND), Module301.23 (GND), Module301.32 (GND), Module301.33 (GND), Module301.42 (GND), Module301.43 (GND), Module301.52 (GND), Module301.53 (GND), Module301.59 (GND), Module301.60 (GND), Module301.65 (GND), Module301.66 (GND), Module301.71 (GND), Module301.74 (GND), Module301.98 (GND), Module302.107 (GND), Module302.108 (GND), Module302.113 (GND), Module302.114 (GND), Module302.119 (GND), Module302.120 (GND), Module302.125 (GND), Module302.126 (GND), Module302.131 (GND), Module302.132 (GND), Module302.137 (GND), Module302.138 (GND), Module302.144 (GND), Module302.150 (GND), Module302.155 (GND), Module302.156 (GND), Module302.161 (GND), Module302.162 (GND), Module302.167 (GND), Module302.168 (GND), Module302.173 (GND), Module302.174 (GND), Module302.179 (GND), Module302.180 (GND), Module302.185 (GND), Module302.186 (GND), Module302.191 (GND), Module302.192 (GND), Module302.197 (GND), Module302.198 (GND); also elsewhere on the board

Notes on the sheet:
CM mechanicals
[CM5]

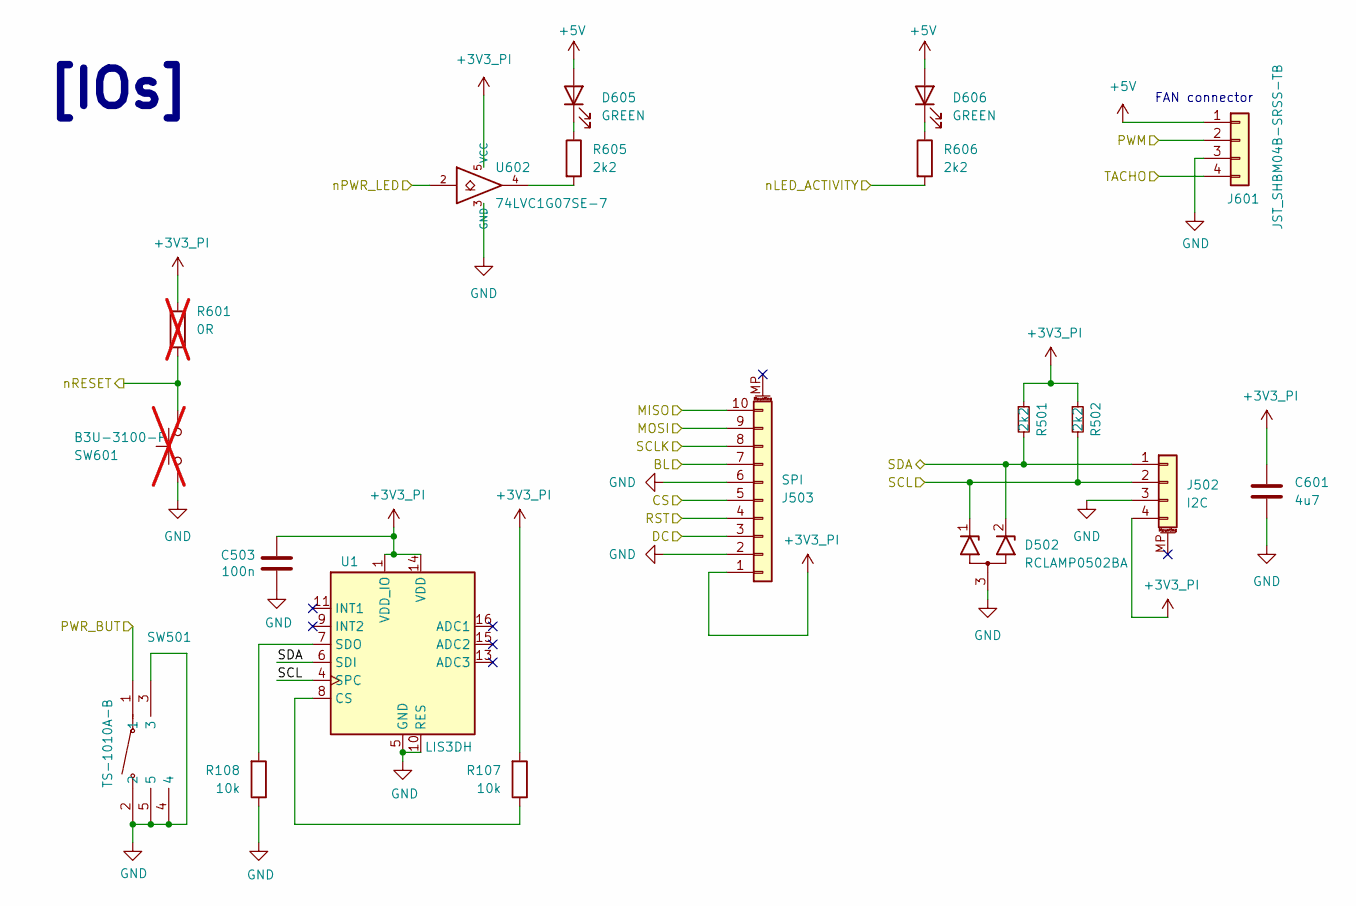
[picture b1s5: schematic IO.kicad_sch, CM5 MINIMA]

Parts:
C503: 100n; C_0402_1005Metric; Part Description 0.1uF 10% 16V Ceramic Capacitor X7R 040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
C601: 4u7; C_0805_2012Metric; Part Description 4.7uF 10% 10V Ceramic Capacitor X7R 080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
D502: RCLAMP0502BA; SOT-416
D605, D606: GREEN; LED-SMD_L1.7-W0.6-RD
J502: I2C; JST_SH_BM04B-SRSS-TB_1x04-1MP_P1.00mm_Vertical
J503: SPI; JST_SUR_BM10B-SURS-TF_1x10-1MP_P0.80mm_Vertical
J601: JST_SHBM04B-SRSS-TB; JST_SH_BM04B-SRSS-TB_1x04-1MP_P1.00mm_Vertical; Part Description 4 pin vertical 1mm pitch connector
R107, R108: 10k; R_0402_1005Metric
R501, R502, R605, R606: 2k2; R_0402_1005Metric
R601: 0R; R_0402_1005Metric; not fitted
SW501: TS-1010A-B; SW-SMD_TS-1010A-B; LCSC Part C381059
SW601: B3U-3100-P; SW_SPST_B3U-3100P-B; not fitted
U1: LIS3DH; LGA-16_3x3mm_P0.5mm_LayoutBorder3x5y
U602: 74LVC1G07SE-7; Diodes_74LVC1G07SE7_SOT353; Part Description Buffer, Non-Inverting 1 Element 1 Bit p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

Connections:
+3V3_PI: C503.1, C601.1, J502.4, J503.1, R107.2, R501.1, R502.1, R601.1, U1.1 (VDD_IO), U1.14 (VDD), U602.5 (VCC); also elsewhere on the board
+5V: D605.2 (A), D606.2 (A), J601.1; also elsewhere on the board
/CM5/BL_GPIO24: J503.7; also elsewhere on the board
/CM5/CS_GPIO18: J503.5; also elsewhere on the board
/CM5/DC_GPI25: J503.3; also elsewhere on the board
/CM5/MISO_GPIO19: J503.10; also elsewhere on the board
/CM5/MOSI_GPIO20: J503.9; also elsewhere on the board
/CM5/PI_nLED_PWR: U602.2; also elsewhere on the board
/CM5/PWM: J601.2; also elsewhere on the board
/CM5/PWR_BUT: SW501.1; also elsewhere on the board
/CM5/RST_GPIO27: J503.4; also elsewhere on the board
/CM5/SCLK_GPIO21: J503.8; also elsewhere on the board
/CM5/TACHO: J601.4; also elsewhere on the board
/CM5/nLED_ACTIVITY: R606.2; also elsewhere on the board
/IO/SCL: D502.1 (K1), J502.2, R502.2, U1.4 (SPC); also elsewhere on the board
/IO/SDA: D502.2 (K2), J502.1, R501.2, U1.6 (SDI); also elsewhere on the board
GND: C503.2, C601.2, D502.3 (A), J502.3, J503.2, J503.6, J601.3, R108.1, SW501.2, SW501.3, SW501.4, SW501.5, SW601.2, U1.5 (GND), U1.10 (RES), U1.12 (GND), U602.3 (GND); also elsewhere on the board
unnamed: D605.1 (K), R605.1
unnamed: D606.1 (K), R606.1
unnamed: R601.2, SW601.1
unnamed: R605.2, U602.4
unnamed: R107.1, U1.8 (CS)
unnamed: R108.2, U1.7 (SDO)

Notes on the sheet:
[IOs]
FAN connector

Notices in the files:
parts and their libraries:
License: Apache-2.0
